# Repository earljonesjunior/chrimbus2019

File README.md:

# chrimbus2019

more information here:
oakst.io/projects/xmas-2019

![schematic][schematic]

![pcb][pcb]

![final][final]

[pcb]: pcb.png "PCB"
[schematic]: schematic.png "Schematic"
[final]: final.jpg "Final Product"

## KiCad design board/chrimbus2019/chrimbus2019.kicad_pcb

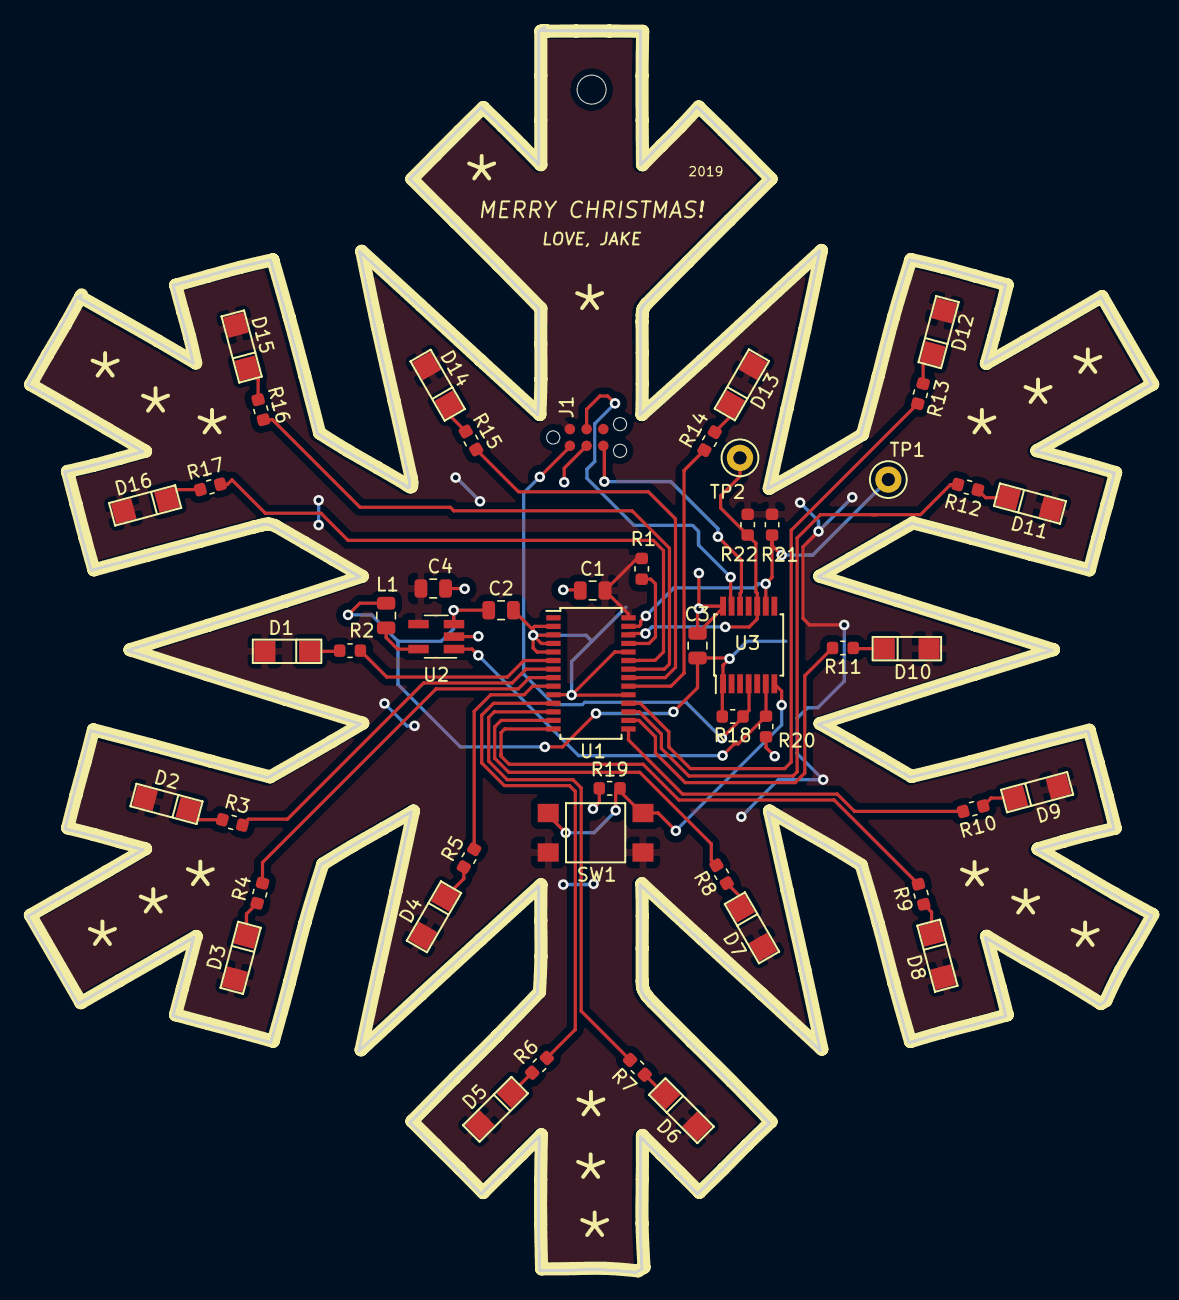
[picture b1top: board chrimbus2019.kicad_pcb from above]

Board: 2 copper layers, 85.4 x 94.6 mm, 52 parts (1 on the bottom side), 44 nets.

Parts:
BT1: CR2450; BAT_BK-877
C1, C2, C3: 0.1uF; C_0805_2012Metric
C4: 10uF; C_0805_2012Metric
D1, D2, D3, D4, D5, D6, D7, D8, D9, D10, D11, D12, D13, D14, D15, D16: LED; LTST-C150AKT
J1: Conn_01x06; Tag Connect
L1: 4.7uH; L_0805_2012Metric
MH1: MountingHole; MountingHole_2.2mm_M2
R1, R20, R21, R22: 10k; R_0603_1608Metric
R2, R3, R4, R5, R6, R7, R8, R9, R10, R11, R12, R13, R14, R15, R16, R17, R18: 150; R_0603_1608Metric
R19: 10K; R_0603_1608Metric
SW1: SW_Push; TL3305AF160QG
TP1, TP2: TestPoint; TestPoint_Keystone_5000-5004_Miniature
U1: TLC59116F; TSSOP-28_4.4x9.7mm_P0.65mm
U2: XC9142; SOT-23-5_HandSoldering
U3: PIC16F15325; TSSOP-14_4.4x5mm_P0.65mm

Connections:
+3V3: C1.2, C4.2, D1.2, D2.2, D3.2, D4.2, D5.2, D6.2, D7.2, D8.2, D9.2, D10.2, D11.2, D12.2, D13.2, D14.2, D15.2, D16.2, J1.2, R1.2, R21.2, R22.2, SW1.1, U1.28, U2.4
+BATT: BT1.1, C2.1, C3.1, L1.1, R18.2, U2.3, U3.1
/CE: R20.1, U2.1, U3.6
/ICSPC: J1.5, U3.12
/ICSPD: J1.4, U3.13
/MCLR: J1.1, R18.1, U3.4
/SCL: R22.1, TP2.1, U1.26, U3.10
/SDA: R21.1, TP1.1, U1.27, U3.9
GND: BT1.2, C1.1, C2.2, C3.2, C4.1, J1.3, R19.1, R20.2, U1.2, U1.3, U1.4, U1.5, U1.10, U1.19, U1.24, U2.2, U3.14
unnamed: D1.1, R2.1
unnamed: D2.1, R3.1
unnamed: D3.1, R4.1
unnamed: D4.1, R5.1
unnamed: D5.1, R6.1
unnamed: D6.1, R7.1
unnamed: D7.1, R8.1
unnamed: D8.1, R9.1
unnamed: D9.1, R10.1
unnamed: D10.1, R11.1
unnamed: D11.1, R12.1
unnamed: D12.1, R13.1
unnamed: D13.1, R14.1
unnamed: D14.1, R15.1
unnamed: D15.1, R16.1
unnamed: D16.1, R17.1
unnamed: L1.2, U2.5
unnamed: R1.1, U1.25
unnamed: R2.2, U1.6
unnamed: R3.2, U1.7
unnamed: R4.2, U1.8
unnamed: R5.2, U1.9
unnamed: R6.2, U1.11
unnamed: R7.2, U1.12
unnamed: R8.2, U1.13
unnamed: R9.2, U1.14
unnamed: R10.2, U1.15
unnamed: R11.2, U1.16
unnamed: R12.2, U1.17
unnamed: R13.2, U1.18
unnamed: R14.2, U1.20
unnamed: R15.2, U1.21
unnamed: R16.2, U1.22
unnamed: R17.2, U1.23
unnamed: R19.2, SW1.2, U3.7

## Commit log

2019-11-07 pre wsmr
2019-12-19 pre sleep mode
2019-12-20 van updates
2020-07-20 pushed changes from final rev
2020-07-20 readme update
2023-06-10 backups
